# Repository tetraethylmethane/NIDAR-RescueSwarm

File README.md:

<h1 align="center">NIDAR RescueSwarm</h1>

<p align="center">
  Three autonomous drones that search a flood zone, find survivors, geotag them,<br>
  and drop medical kits — with no network, no pilot, and one operator who only presses start.
</p>

<p align="center">
  <b>NIDAR 2026–27 · Track 1 · Mission 1</b><br>
  <sub>MeitY · Drone Federation of India · SwaYaan</sub>
</p>

---

## 1. Status

**Phase 0/1.** Sized end to end, requirements baselined against the rulebook, and the ground station runs as a system against three real ArduCopter SITL autopilots.

**What exists:** coverage planner, geotag geometry and its error model, ArduPilot parameter sets, safety-link protocol, ground station. All tested — 129 + 17 + 67 tests, 13 committed model outputs.

**What does not:** the aircraft, and the detector. There is **no camera anywhere in the loop**; survivors have only ever come from a simulator. Nothing has flown on hardware.

<p align="center">
  
  <br>
  <sub>Three real autopilots flying the coverage planner's output in AUTO, in 6 m/s wind, over locally cached imagery. Every number came from an autopilot.<br>
  ▶ <a href="ground-station/mission-flight.mp4">mission-flight.mp4</a> · <a href="ground-station/README.md">ground-station/README.md</a></sub>
</p>

### Next actions

| # | Action | When | Why first |
|:--|:--|:--|:--|
| 1 | [Send the organiser questions](docs/requirements/organiser-questions.md) — drafted | This week | External latency; nothing else here has any |
| 2 | Start collecting recall data | P1 | The long pole. 250 points, irreducible calendar cost |
| 3 | Bench the cold-boot timing | P1 | The only constraint under 20 % margin, still modelled |

Registration Aug 2026 · reviews Oct and Dec · **finals Jan 2027**. About 21 weeks, but monsoon and exams cut the **flight-test window to ~8 weeks**. See the [development plan](docs/development-plan.md).

---

## 2. Design point

Outputs of a closed model in [`tools/sizing-model/`](tools/sizing-model/), reconciled with the BOM to ~2 %.

| Aircraft | | Mission | |
|:--|:--|:--|:--|
| Configuration | Quadrotor · 18 in CF folding props | Design mission | **7.7 min** of 30 |
| Battery | 6S3P 21700 · 18 cells · 292 Wh | Search | 60 m AGL at 8 m/s |
| MTOW | 6.36 kg *(model)* · 6.23 kg *(BOM)* | Sweep | 93 s/drone, 10 ha over 3 |
| **Fleet** | **19.1 kg** of 25 kg — 24 % margin | GSD | 1.82 cm/px — a person is ~93 px |
| Hover | 913 W · 9.7 kg/m² disk loading | Link | ≥13 dB at 600 m · 2.5 Mbps |
| Endurance | 15.3 min — **≈2.0× the mission** ⚠ | Geotag target | CEP50 ≤ 0.75 m with RTK |
| Thrust-to-weight | 2.0 static · hover at 50 % | Delivery target | ≥60 % within 2 m, ≥30 % within 1 m |

> ⚠ **The reserve is spent.** The 300 g parachute (SYS-41) takes endurance to ≈2.0× against a self-imposed ≥2.0× policy. Any further mass growth breaks it. See [`bom_reconcile.py`](tools/sizing-model/bom_reconcile.py).
>
> **Under review:** 40 m beats 60 m — 140 px on a person instead of 93, for 2.5 min of a 15 min allowance. Pending recall measurement in P7.

---

## 3. Proof

Three ArduCopter SITL instances, the real `rescueswarm-drone{1,2,3}.parm`, the real planned missions. Every number below came off MAVLink. Telemetry is committed in [`simulations/recordings/`](simulations/recordings/); the figures redraw from it.

### 3.1 The battery failsafe brings them home

`BATT_FS_LOW_ACT = 2` had been reviewed and unit-tested for weeks, and **no simulation ever loaded the file** — every SITL script used stock defaults, where the value is `0` and a low battery does nothing at all. Now proven end to end: RTL fires at **10 809 mAh of a 10 800 mAh trip**, on all three aircraft, within two seconds of each other.

### 3.2 They no longer collide

Three defects, none visible in review, all found by running the real artifact:

- **Launches were simultaneous.** Three aircraft leaving slots 1.22 m apart measured 1.3 m from each other at 2–3 m altitude. Now `NAV_DELAY` 0/15/30 s in the mission file.
- **Two of three swept the wrong way round**, finishing 516 m and 540 m from the pad on the lowest state of charge of the flight, because sweep direction keyed on drone index. Now all three finish inside 130 m, same path length.
- **They landed on top of each other.** See §4.

| Separation, three aircraft | Before | After |
|:--|--:|--:|
| Launch, closest pair | 1.31 m | **26.96 m** |
| Whole flight, both airborne | 3.99 m | **5.51 m** |
| Closest horizontal, any time | 0.83 m — *overlap* | **1.89 m** |
| Recovery run, closest at any time | 0.83 m — *overlap* | **2.27 m** |

### 3.3 The search pattern

Each strip is swept twice, the second pass on the reverse heading, and every sweep finishes near the pad.

### 3.4 The pad

> **"Measured" means measured in simulation.** That rules out whole classes of error and none of the physical ones. [HANDOFF.md](HANDOFF.md) §2 keeps measured, modelled and assumed apart.

---

## 4. Decisions

| Decision | Outcome | Why |
|:--|:--|:--|
| Coaxial X8? | **Rejected** | +59–119 % hover power, +34–50 % fleet mass, cuts the margin to 2 %, buys no footprint back, worst attitude bandwidth tested |
| Rotor count | **Quad** | Hex/octo match or beat it on physics, but cost 1.5–2× the propulsion integration on a 21-week calendar. Decided on schedule risk, not physics |
| Prop diameter | **18 in** | Matches the BOM, and better than 20 in on descent (0.42 v_i) and gust sensitivity (0.168) |
| Thrust-to-weight | **2.0** | Tilt only reaches 12° at 15 m/s — attitude authority is never the wind limit |
| Recovery chute | **Fit one** | Cannot meet the "land on the pad" condition, but −10 beats −50, so it is worth ~40 points anyway |
| Pad layout | **Corners, not a row** | A row is the worst packing on a square. Compliance said "3 per row"; they landed **0.83 m** apart — an overlap. Corners give 2.61 m instead of 1.22 m. Measured closest approach **0.83 → 2.27 m** |
| Search pattern | **Two passes, second reversed** | Not for coverage — one pass has no gaps. Boresight bias is *systematic*, so flying the reverse heading cancels it where more frames cannot. Costs a full second sweep |
| Launch and recovery | **Sequenced in the mission file** | `NAV_DELAY` 0/15/30 s and `RTL_LOIT_TIME` 0/60/120 s — parameters, not companion code, because the failsafe RTL is a mode change inside the flight controller. The loiter stagger is 60 s because the descent was **measured** at 53 s; at the 20 s it was first set to, two aircraft closed to 3.10 m over the pad |
| Motor-out redundancy | **Open** | Only rotors keep the aircraft *flying and scoring*, and only rotors work in the 6 m delivery hover. Ties to rotor count |

Numbers in [configuration trade](docs/sizing/configuration-trade.md).

---

## 5. Scoring, and what reading it properly changed

**1000 points:** 600 flight · 200 design review · 200 business strategy.

| Flight — 600 | Points | | Penalty | Cost |
|:--|--:|:--|:--|--:|
| Detection + geotagging | **250** | 25 each, max 10 | Manual input or reset | −50 |
| Kit delivery accuracy | **200** | ≤1 m: 20 · ≤2 m: 14 · ≤3 m: 8 | Crash | −50 |
| Multi-drone collaboration | 50 | binary | Geofence breach | −20 |
| Single GCS interface | 50 | binary | Landing outside the box | −10/drone |
| Finish inside 15 min | 50 | binary | <sub>capped at 150</sub> | |

Three findings that moved the design more than any engineering analysis did:

- **Geolocation gates 450 of 600 points**, not 250. Kits are scored from the survivor, so a drop is never better than the tag it aimed at. RTK alone is worth 82 delivery points.
- **We were designing to the worst zone.** The old ≤3 m target scored 8 of 20 per drop; the old "90 % within 5 m" requirement sat outside every zone and would have scored nothing.
- **Speed is worth 50 points and is already won.** The bonus needs 15 min; we fly 7.7. Spend the surplus on recall — fly lower, take more looks.

Full breakdown in [rulebook compliance](docs/requirements/rulebook-compliance.md).

---

## 6. Open

| Risk | Detail | Status |
|:--|:--|:--|
| **Setup margin** | 15 s against a 5-minute rule — modelled, not measured | Recovered by SYS-42/43; bench in P1 |
| **VRS on every delivery** | 2.5 m/s descent sits at 0.48 v_i, on the vortex-ring boundary | Fix in the flight profile, not the airframe |
| **Wind cliff at 8 m/s** | Search groundspeed is 8 m/s, so at that windspeed we make no headway. Wind is natural and uncapped | Requirement: 10 m/s headway (SYS-37) |
| **Business strategy** | 200 points, barely started; sponsorship evidence cannot be produced in the final week | Start now |

Four questions are [drafted and unsent](docs/requirements/organiser-questions.md) — how "correctly geotagged" is verified, whether a canopy descent scores −10 or −50, whether motor-out tolerance is required, and whether the pad can be surveyed beforehand. The first decides whether ~1–2 m of absolute base error costs anything against 250 points. Answers already received are recorded in the same file.

---

## 7. Repository

```text
HANDOFF.md                  read this first if you are picking the project up
TRAPS.md                    read this before adding a config, a generated file or a test
docs/                       requirements, sizing, business, system overview
tools/sizing-model/         the model everything traces back to
hardware/bom/               Indian BOM + indigenisation scorecard
autonomy/coverage_planner/  boundary in, one AUTO mission per drone out
perception/geotagging/      pixel to lat/lon, and a Monte Carlo of its error
firmware/ardupilot-params/  the five failsafes, as parameters not code
simulations/                SITL harness, committed telemetry, figures
ground-station/             mission_backend + the GCS engineering record
```

The **running** ground station — Flask server, React client, SITL launch scripts — is in [NIDAR-GSC](https://github.com/tetraethylmethane/NIDAR-GSC). What lives here is `ground-station/mission_backend/` (fleet model, KML parser, MAVLink ingest, and the SYS-20 module split that makes a retask route structurally unreachable), plus the requirement evidence: [PLAN.md](ground-station/PLAN.md), the flight screenshots and [mission-flight.mp4](ground-station/mission-flight.mp4).

> ⚠ **The two copies of `mission_backend` have drifted.** `mavlink_ingest.py` is 186 lines here against 304 in NIDAR-GSC, and only the GSC copy calls `SET_MESSAGE_INTERVAL` — without which a passive listener receives nothing but heartbeats. The GSC copy is the one that flies; this one is what CI tests. See [HANDOFF.md](HANDOFF.md) §4.5.

`communication/` is still planned.

```bash
pip install -r tools/sizing-model/requirements.txt
python3 tools/sizing-model/rescueswarm_sizing_model.py   # the design point
python3 tools/sizing-model/bom_reconcile.py              # read before ordering

export NIDAR_SYS=$PWD
../NIDAR-GSC/scripts/test-battery-failsafe.sh            # low battery brings it home
python3 simulations/sitl/fly_and_record.py               # three aircraft fly the plan
python3 simulations/sitl/proof_figures.py                # redraw §3 from telemetry
```

`NIDAR_SPEEDUP=3` slows the sim enough to see the launch stagger. Do **not** use `NIDAR-GSC/scripts/run-sim.sh` — it launches a fixed wing with no project parameters.

> **Change the model, re-run it, commit the new output in the same commit.** Every number in this README traces to [`docs/sizing/`](docs/sizing/), and CI fails if one drifts.

| Document | What's in it |
|:--|:--|
| [Handoff](HANDOFF.md) | **Start here.** What is proven, what waits on a human, what is unowned |
| [Traps](TRAPS.md) | Ten classes of defect this project has already paid for, and what now prevents each |
| [Competition day](docs/checklists/competition-day.md) | How the GCS is actually operated on the day — draft, never rehearsed |
| [System overview](docs/system-overview.md) | Mission flow, architecture, perception, indigenisation, failsafes |
| [Sizing calculations](docs/sizing/sizing-calculations.md) | Why every number is what it is |
| [Requirements baseline](docs/requirements/requirements-baseline.md) | Every SYS-xx requirement, traced to a rule and a verification method |
| [Rulebook compliance](docs/requirements/rulebook-compliance.md) | Rule-by-rule matrix, scoring, conflicts |
| [Development plan](docs/development-plan.md) | Schedule, critical path, risk and de-scope order |
| [Implementation plan](docs/implementation-plan.md) | What to build for autonomy, perception and failsafes — and what can be skipped |
| [Frame design constraints](docs/frame-design-constraints.md) | What CAD needs before the first part is cut |

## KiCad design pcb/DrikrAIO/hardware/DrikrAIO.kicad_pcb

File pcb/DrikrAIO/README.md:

# DrikrAIO — Stage 1

Single-board integration of a flight controller, four ESC channels and an
ExpressLRS receiver, assembled from proven OpenDrone designs.

**Status: schematic netlists; board is a placed scaffold, unrouted.** See *Open work*.

This is Stage 1 of two. It deliberately targets FPV-class hardware on the parts
that already fly, to prove the integration once. Stage 2 re-platforms to
ArduPilot on a Pixhawk Autopilot Bus carrier and reuses the power tree, ESC
block and layout zoning proven here.

## Licence and attribution

**CERN-OHL-S-2.0, strongly reciprocal**, inherited from the upstream sources.
Every sheet in `hardware/` is copied from an [OpenDrone-hw](https://github.com/OpenDrone-hw)
project by @Just4Stan / incutec. This board is a derivative work; its complete
sources are published under the same licence, as that licence requires.

| Sheet | Copied from | Upstream status |
|---|---|---|
| `rp2350a`, `power`, `imu`, `osd`, `blackbox`, `pads` | OpenFC-Lite-Mini rev3.3 | Shipping. Rev2 flown. |
| `ESC` (×4) | OpenESC-30x30 rev3.3 | Shipping. Rev1 validated build. |
| `rx_esp32c3_sx1281` | OpenAIO (itself from OpenRX-Lite) | Routed, never manufactured |
| `esc_power` | OpenESC-30x30 rev3.3 root sheet | Shipping |
| `KiCad-Library/` | OpenDrone-hw/KiCad-Library | Shared parts catalogue |

## Design decisions

**40 V MOSFETs, not 30 V.** OpenAIO uses the DOY180N03T, 30 V, which on a 6S
pack at 25.2 V leaves 1.19× margin — below what half-bridge ringing reaches.
The `ESC` sheet is taken from OpenESC-30x30 instead, which uses the 40 V
SP40N01GHNK at 1.59× and is rated to 8S. This is why the ESC sheet comes from
the 30×30 rather than from OpenAIO.

**30.5 × 30.5 mm mount.** Four PDFN-8L 5×6 power stages do not fit on OpenAIO's
25.5 mm — that is precisely why upstream used the smaller 30 V part. The larger
mount also removes the crowding that left OpenAIO with 74 unrouted pads.

**Two power trees, kept separate.** The FC sheet makes +10 V, +5 V, +3V3 and
+1V8; the ESC needs its own +10 V gate rail and +3V3. They are **not** merged.
The FC's +10 V is gated by `10V_ENABLE` (a firmware PINIO, there to switch a
VTX), and a firmware toggle that cuts gate drive in flight is not a rail an ESC
may share. The ESC keeps the LMR54406 buck and TLV76733 LDO from OpenESC-30x30.

**SX1281, 2.4 GHz.** Not the dual-band LR1121. The 865–867 MHz safety link
([`communication/safety_link/`](../../communication/safety_link/)) must be a
physically separate radio: the reason to abort is usually that the primary link
has failed, so an abort path sharing that radio is not an abort path.

## Reference bands

Each sheet numbers into its own band, so a reference says which block it is in
and nothing collides. The four ESC channels share one file and are distinguished
by band.

| Band | Sheet | | Band | Sheet |
|---|---|---|---|---|
| 1xx | rp2350a | | 6xx | pads |
| 2xx | power | | 7xx | rx |
| 3xx | imu | | 11xx | ESC channel 1 |
| 4xx | osd | | 12xx | ESC channel 2 |
| 5xx | blackbox | | 13xx | ESC channel 3 |
| 8xx | esc_power | | 14xx | ESC channel 4 |

## State

```
components 347      nets 332      sheets 12
ERC        30 errors, 546 warnings
```

**The 30 errors are inherited, not introduced.** The donor boards report the
same classes: OpenFC-Lite-Mini, which has flown, reports 8 `power_pin_not_driven`,
and OpenESC-30x30, in production, reports 24 `pin_not_driven` and 3
`power_pin_not_driven`. Summed across what we instantiate, the donor baseline is
about 37; this design sits below it. `PWR_FLAG`s were tried on +BATT and GND and
removed again -- they cleared none of the old errors and added two new
`label_dangling`, and a new error type is a regression where an existing one is
not. Resolve these in KiCad against the real symbols.

Most of the warnings are the same story: `pin_to_pin` inherited from the donor
sheets, plus unresolved `ESCLibrary` / `PCM_*` symbol libraries, which are KiCad
PCM add-ons. Symbols are embedded in the schematics, so the design opens and
netlists without them; install them only to re-place those parts.

## Board

`DrikrAIO.kicad_pcb` exists as a **scaffold, not a layout**. 50 x 50 mm on the
30.5 mm mounting pattern, 6 layers, 2 oz outer / 1 oz inner, ENIG. Nothing is
routed.

```
50 x 50 mm      6 layers      347 footprints      1283 pads netted
292 placed on board            55 staged off-board, grouped by block
0 overlaps                     0 parts crossing the edge
```

Placement is by function: power stages in four quadrants on the bottom with
the shared power block across the middle, control on top, receiver in a corner
for the antenna. Where a zone filled up the remainder is staged **outside** the
outline in per-block columns, which is what KiCad does with new parts -- better
an honestly unplaced part than one silently overlapping its neighbour.

**Board size was measured, not chosen.** U3's pad set alone spans 44.0 x 45.8 mm
so 45 mm could not contain it, and the other 346 parts come to 2409 mm2 of
footprint area -- 48 % of a two-sided 50 mm board, which leaves room to route.

Rebuild it with:

```sh
"C:/Program Files/KiCad/10.0/bin/python.exe" hardware/tools/build_pcb.py
```

## Reviews

# ROUTING STATUS: BLOCKED — BASELINE FROZEN

**[docs/routing-readiness-report.md](docs/routing-readiness-report.md) is current.**
Baseline rev 3, frozen: [docs/pre-routing-baseline.json](docs/pre-routing-baseline.json),
[docs/freeze-manifest.json](docs/freeze-manifest.json).

Verify the freeze at any time:

```sh
python hardware/tools/freeze.py     # exit 0 = intact
```

Primary remaining thermal variables are **airflow exposure and duty cycle**.
More copper is **not** the primary solution.

Blocked on: 115 A peak duration, peak repetition rate, airflow boundary
condition, thermal validation plan, and the deferred MOSFET schematic commit.

**Thermal is MARGINAL, not PASS.** Only one steady-state case passes — hover in
developed slipstream (103.2 C). Peak fails the 125 C target at both airflows
(132.7 C slipstream, 169.9 C at the disc). Still air reaches 393 C and is
prohibited above quiescent.

The result that redirects the work: Rth(j-c) + R_spread contribute only **5.7 K**
of the rise. **More vias and more copper cannot fix the peak case** — the
bottleneck is board-to-air. The only levers are airflow exposure and duty cycle.

The result that may make it moot: board time constant is **31-45 s**, so a peak
much shorter than that barely moves the board. At h=60, duty up to 0.5 stays
under target. But duty cycle is OPEN, so no row can be selected.

Analysis: [docs/thermal-analysis.md](docs/thermal-analysis.md) ·
Validation: [docs/thermal-validation-plan.md](docs/thermal-validation-plan.md)

## Electrical design review

**[docs/electrical-design-review.md](docs/electrical-design-review.md) gates
routing.** Numbers regenerate from `hardware/tools/power_review.py`.

**Resolved:** `Phase` and `VBAT` netclasses corrected 1.0 mm → 6.6 mm with
0.8/0.4 vias (1.0 mm carries 5.3 A against a 21 A phase RMS), and the MOSFET
decision is **60 V minimum**.

**Preferred part: Infineon BSC014N06NS**, verified against the manufacturer
datasheet (Rev 2.6) in [docs/pre-routing-report.md](docs/pre-routing-report.md).
Package is **PG-TDSON-8**. Land pattern **passes** the arithmetic against
`PDFN-8L_L6.0-W5.0-P1.27`; the **stencil does not** — the thermal pad has one
18 mm² paste aperture where Infineon specifies a windowpane, a defect the
current OpenESC footprint already carries. Loop budget corrected to **8.72 nH**
on the real t_f of 11 ns, 3.9× the 40 V part. Not committed to the schematic.

**The headline current is not board capability:** 257 A is at T_c=25 °C. On a
PCB in still air the datasheet says **31 A**, assuming 6 cm² of copper per
device — and 24 FETs on a 50 × 50 board get about 2.1 cm² each.

**Still open: the 115 A peak duration** is undefined anywhere in the repo, so
repeated peaks cannot be assessed. Firmware parameter, not a PCB one.

Also established: 115 A needs 69 mm of 2 oz outer copper on a 50 mm board, so
the bus must use **all six layers**; J1 is 0.7 A per contact and is a breakout
only, never a battery path; and the board is cooled by propwash — at peak in
still air it reaches ~110 °C.

## Open work

1. **Routing, and real placement.** The scaffold groups parts correctly; it does
   not lay them out. Four switching power stages, a 2.4 GHz chain and a 115 A
   battery entry share this board, and that is judgement work, not a generator's.
   Start by pulling the 55 staged parts in and putting the IMU near the board
   centre -- the scaffold parks it at the right edge for want of a free zone.
2. **Review the generated root in KiCad.** `DrikrAIO.kicad_sch` was produced by
   a script, not drawn. It wires sheets with global labels on stubs, which is
   electrically correct and reviewable, but it is not a drawn schematic.
3. **Resolve the 30 inherited ERC errors** against the real symbols, or record
   them as accepted the way the donor projects do.
4. **`+3.3V` and `+3V3` are different nets** -- the FC rail and the ESC rail,
   deliberately separate per the power-tree decision above. The names differ by
   one character and mean different things, which is a trap. Consider renaming
   the FC rail to `+3V3_FC` before layout.

### Done

Board power entry, ESC current sense and the motor pads all arrived with
`esc_power`. `U3` in that sheet is not a board outline -- an earlier pass
mistook it for one and deleted it -- it is the ESC's whole pad set: VBAT,
BATGND, CUR, M1-M4 and the twelve phase pads 1A..4C. Verified in the netlist:
`ESC_CURRENT` reaches the FC ADC, `+10V` reaches all four gate-driver rails,
`M1_A` runs from the channel-1 MOSFETs to its pad, and `MOTOR1` runs from the
FC MCU to the channel-1 DShot input.

## Build

Every sheet here is a rewritten copy of a donor. That rewrite is not
idempotent, so rebuild the whole set rather than editing in place:

```sh
bash hardware/tools/regen.sh
```

```sh
kicad-cli sch erc hardware/DrikrAIO.kicad_sch
kicad-cli sch export netlist --format kicadsexpr -o /tmp/DrikrAIO.net hardware/DrikrAIO.kicad_sch
```

Requires KiCad 10. The files are KiCad 10 format and KiCad 8 cannot open them.

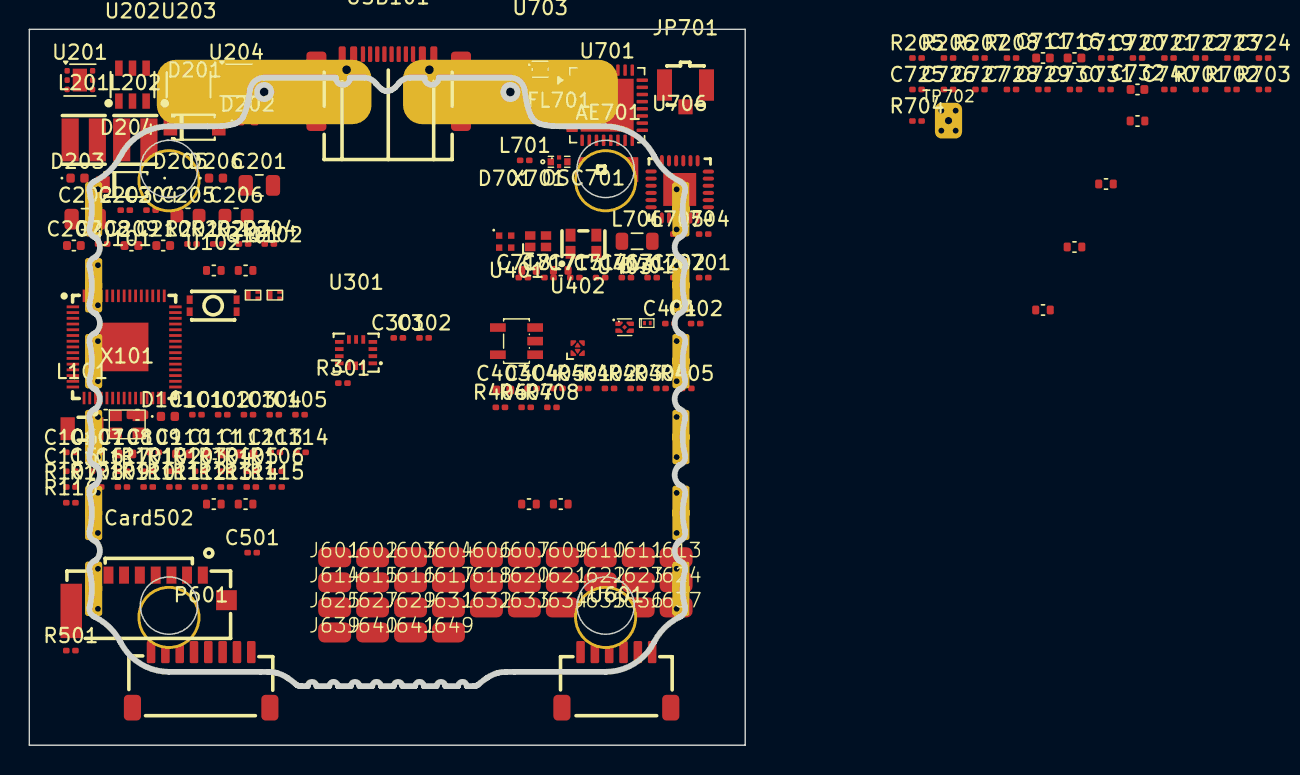
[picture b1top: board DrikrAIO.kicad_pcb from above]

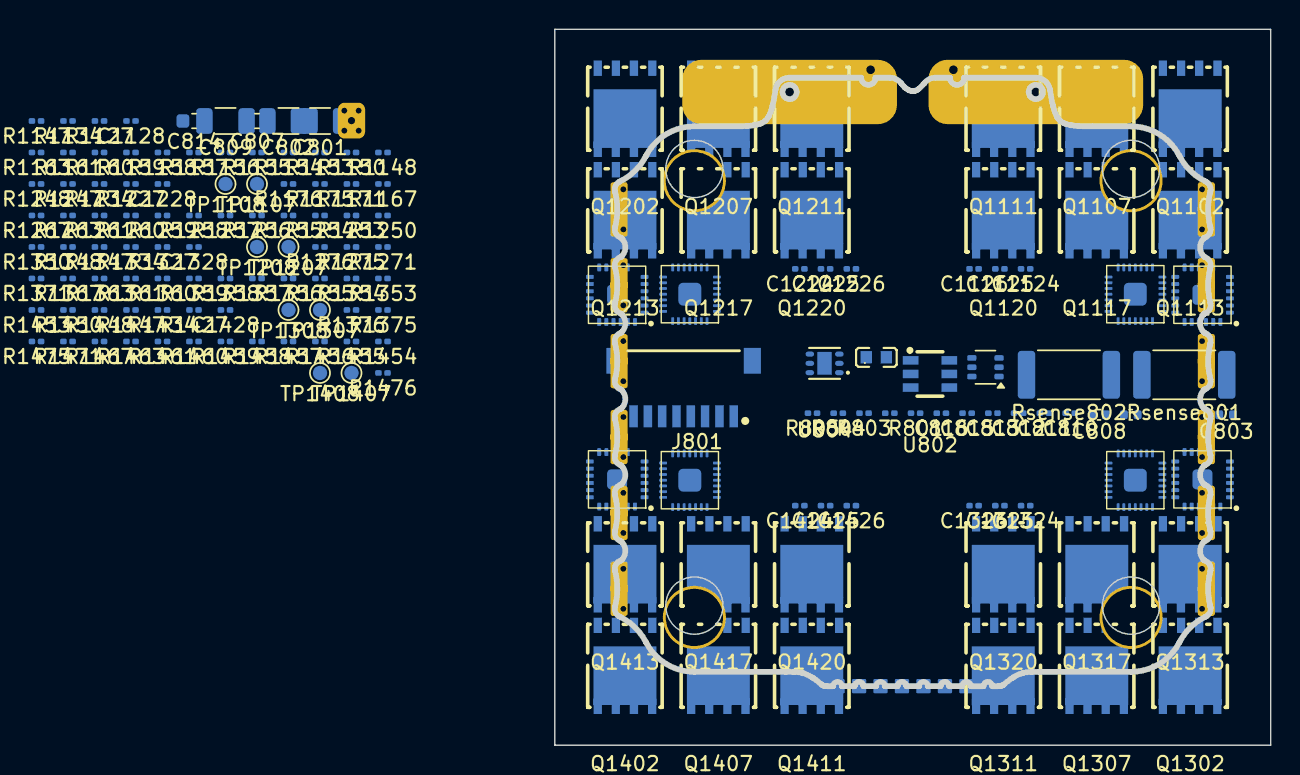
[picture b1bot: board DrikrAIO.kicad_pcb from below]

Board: 6 copper layers, 50.0 x 50.0 mm, 347 parts (173 on the bottom side), 243 nets, no tracks yet.

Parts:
AE701: 2450AT18A100E; ANT-SMD_L3.2-W1.6
C101, C103, C104, C105, C106, C107, C109, C113, C115, C116, C117, C203, C204, C208, C301, C302, C402, C404, C405, C501: 100n; C_0201_0603Metric
C102, C114: 20p; C_0201_0603Metric
C108, C110, C111, C112, C207: 4.7uF; C_0402_1005Metric
C201, C202: 4.7uF 50v; C_0805_2012Metric
C205, C206, C807, C814: 22uF; C_0603_1608Metric
C209, C210, C803, C808: 22uF; C_0402_1005Metric
C401: 470p; C_0201_0603Metric
C403, C806: 1uF; C_0402_1005Metric
C701, C728: 15pF; C_0201_0603Metric
C702, C715, C722, C724, C727, C729: 1uF; C_0201_0603Metric
C711, C716, C732: 10uF; C_0402_1005Metric
C712, C713, C714, C717, C730, C731, C740, C810, C811, C812, C813, C815, C816, C1124, C1125, C1126, C1128, C1224, C1225, C1226, C1228, C1324, C1325, C1326, C1328, C1424, C1425, C1426, C1428: 100nF; C_0201_0603Metric
C718: 1nF; C_0201_0603Metric
C719: 470nF; C_0201_0603Metric
C720, C721: 1.2pF; C_0201_0603Metric
C723, C725, C726: 10nF; C_0201_0603Metric
C801, C802, C809: 4.7uF; C_1206_3216Metric
C804, C805, C1104, C1108, C1127, C1204, C1208, C1227, C1304, C1308, C1327, C1404, C1408, C1427: 100nF; C_0402_WIDE
Card502: TF-021B-H265; TF-SMD_TF-021B-H265
D101: LED_1_Blue; LED_0402_1005Metric
D201, D204: DSK24; SOD-123_L2.8-W1.8-LS3.7-RD
D202, D203, D205, D206: LED_1_Green; LED_0402_1005Metric
D401: SDM02U30LP3-7B; X3-DFN0603-2_L0.6-W0.3-RD
D701: XL-1010RGBC-WS2812B; LED-SMD_4P-L1.0-W1.0-TL_XL-1010RGBC-WS2812B
FL701: 2450FM07D0034T; FILTER-SMD_4P-L1.0-W0.5-L
J601, J602, J603, J604, J606, J607, J609, J610, J611, J613, J614, J615, J616, J617, J618, J620, J621, J622, J623, J624, J625, J627, J629, J631, J632, J633, J634, J635, J636, J637, J639, J640, J641, J649: 5V; small_pad
J801: SM08B-SRSS-TB; JST_SM08B-SRSS-TB
JP701: U.FL-R-SMT-1(80); RF-SMD_FRF05002-JSS103M
L101: AOTA-B201610S3R3-101-T; IND-SMD_L2.0-W1.6_AOTA-B201610S3R3-101-T
L201, L202: XRTC303020D4R7MBCA; IND-SMD_L3.0-W3.0_AFE303020S
L701: 24nH; L_0201_0603Metric
L704: 2.5nH; L_0201_0603Metric
L705: 2.0nH; L_0201_0603Metric
L706: 15uH; L_0805_2012Metric
OSC701: OW7EL89CENUNFAYLC-52M; OSC-SMD_4P-L2.0-W1.6-BL_TXC_7Z
P601: SM08B-SRSS-TB(LF)(SN); CONN-TH_SM08B-SRSS-TB-LF-SN
Q101, Q102: AP1606; DFN-3L_L1.0-W0.6-P0.65-BR
Q1102, Q1107, Q1111, Q1113, Q1117, Q1120, Q1202, Q1207, Q1211, Q1213, Q1217, Q1220, Q1302, Q1307, Q1311, Q1313, Q1317, Q1320, Q1402, Q1407, Q1411, Q1413, Q1417, Q1420: SP40N01GHNK; PDFN-8L_L6.0-W5.0-P1.27
R101, R104, R201, R203: 100k; R_0201_0603Metric
R102, R105, R107: 30R; R_0201_0603Metric
R103, R108, R301, R501, R701, R702, R703, R704, R802, R1147, R1148, R1247, R1248, R1347, R1348, R1447, R1448: 10k; R_0201_0603Metric
R106, R109, R114, R115: 5.1k; R_0201_0603Metric
R110, R116: 1k; R_0201_0603Metric
R111, R208: 2.4k; R_0201_0603Metric
R112, R113, R401, R408: 75R; R_0201_0603Metric
R202, R206: 6.49k; R_0201_0603Metric
R204: 13.7k; R_0201_0603Metric
R205: 7.5k; R_0201_0603Metric
R207, R406, R407: 510R; R_0201_0603Metric
R402: 3.9k; R_0201_0603Metric
R403: 12k; R_0201_0603Metric
R404: 1.4k; R_0201_0603Metric
R405: 680R; R_0201_0603Metric
R801: 115k; R_0201_0603Metric
R803, R804, R805, R1154, R1157, R1160, R1254, R1257, R1260, R1354, R1357, R1360, R1454, R1457, R1460: 1k; C_0201_0603Metric
R1127, R1134, R1150, R1163, R1167, R1171, R1227, R1234, R1250, R1263, R1267, R1271, R1327, R1334, R1350, R1363, R1367, R1371, R1427, R1434, R1450, R1463, R1467, R1471: 15R; R_0201_0603Metric
R1153, R1155, R1156, R1158, R1159, R1161, R1253, R1255, R1256, R1258, R1259, R1261, R1353, R1355, R1356, R1358, R1359, R1361, R1453, R1455, R1456, R1458, R1459, R1461: 10k; C_0201_0603Metric
R1175, R1275, R1375, R1475: 220R; R_0201_0603Metric
R1176, R1276, R1376, R1476: 10R; R_0201_0603Metric
Rsense801, Rsense802: 0.2mR; R_2512_6332Metric
TP702: BOOT; SolderPad_1.2x2.0mm
TP1107, TP1108, TP1207, TP1208, TP1307, TP1308, TP1407, TP1408: TestPoint; TestPoint_Pad_D1.0mm
U101: RP2354A; QFN-60_L7.0-W7.0-P0.40-TL-EP3.4
U102: TS2306A 240GF MSM 9_C2976675; SW-SMD_4P-L3.0-W2.0-P0.85-LS3.5
U201: LP5912-1.8DRVR; WSON-6-1EP_2x2mm_P0.65mm_EP1x1.6mm_ThermalVias
U202, U203: LMR51430YFDDCR; SOT-23-6_L2.9-W1.6-P0.95-LS2.9-BL
U204: LP5912-3.3DRVR; WSON-6-1EP_2x2mm_P0.65mm_EP1x1.6mm
U301: BMI270; LGA-14_L3.0-W2.5-P0.50-BR
U401: COS8051SOT; SOT-23-5_L3.0-W1.7-P0.95-LS2.8-BR
U402: SN74LVC1G3157DTBR; X2SON-6_L1.0-W0.8-BL
U403: TLV7031DPWR; X2SON-4_L0.8-W0.8-P0.48-TL-A
U601: SM06B-SRSS-TB(LF)(SN); CONN-SMD_SM06B-SRSS-TB-LF-SN
U701: ESP32-C3; QFN-32-1EP_5x5mm_P0.5mm_EP3.7x3.7mm
U703: TLV75533PDQNR; X2SON-4_L1.0-W1.0-P0.65-TL-EP
U706: SX1281IMLTRT; QFN-24_L4.0-W4.0-P0.50-TL-EP2.6
U801: INA186A3IDCKR; SOT-363_SC-70-6
U802: LMR54406DBVR; SOT-23-6_L2.9-W1.6-P0.95-LS2.8-BR
U803: FTC160808S4R7MBCA; IND-SMD_L1.6-W0.8_FTC160865SR47MBCA
U804: TLV76733DRVR; WSON-6_L2.0-W2.0-P0.65-TL-EP
U805: 4in1ESC30x30
U1101, U1201, U1301, U1401: NSG2065Q; QFN-24_L4.0-W4.0-P0.50-TL-EP2.8
U1108, U1208, U1308, U1408: AT32F421G8U7; QFN-28_L4.0-W4.0-P0.40-TL-EP2.4
USB101: TYPE-C 16P QTWT; USB-TYPE-C-SMD_TYPE-C-16P-QTWT
X101: XTM25012000JT00351001; CRYSTAL-SMD_4P-L2.5-W2.0-BL-A
X701: CJ17-400001010B20; CRYSTAL-SMD_4P-L1.6-W1.2-BL

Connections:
10V_ENABLE: U101.41, U202.5
+1.1V: C101.1, C107.1, C108.1, C112.1, L101.1, U101.6, U101.23, U101.39, U101.50
+1.8V_GYRO: C209.1, C301.1, U201.1, U301.8
+3.3V: C103.1, C104.1, C105.1, C111.1, C113.1, C115.1, C116.1, C117.1, C210.1, C302.1, C402.1, C404.1, C405.1, C501.1, Card502.4, J617.1, R102.1, R114.1, R115.1, R207.1, R301.2, R403.2, R501.1, U101.1, U101.11, U101.20, U101.26, U101.30, U101.38, U101.44, U101.45, U101.49, U101.53, U101.54, U204.1, U301.5, U401.5, U402.5, U403.2
+3V3: C711.1, C712.1, C713.1, C714.1, C715.1, C716.1, C717.1, C722.1, C723.1, C729.1, C730.1, C731.1, C740.1, C803.2, C808.2, C813.1, C815.1, C1126.1, C1226.1, C1326.1, C1426.1, D701.2, L705.2, OSC701.4, R701.1, R702.1, R703.1, R704.2, R1147.2, R1176.2, R1247.2, R1276.2, R1347.2, R1376.2, R1447.2, R1476.2, U701.11, U701.17, U701.18, U701.31, U701.32, U703.1, U706.11, U706.15, U801.3, U804.1, U804.2, U1108.17, U1208.17, U1308.17, U1408.17
+4v5: C207.1, C208.1, C702.1, C732.1, D201.1, D204.1, J631.1, J641.1, R206.1, U201.4, U201.6, U204.4, U204.6, U703.3, U703.4
+5V: C206.1, D204.2, J606.1, J611.1, J614.1, J620.1, L202.2, R111.1, R203.2, R208.1
+5V_USB: D201.2, USB101.A4, USB101.A9
+10V: C205.1, C807.1, C812.1, C814.1, C1128.1, C1228.1, C1328.1, C1428.1, J636.1, L201.2, R201.2, R205.1, R801.1, U601.1, U803.2, U804.4, U804.6, U1101.4, U1201.4, U1301.4, U1401.4
+BATT: C201.1, C202.1, C801.1, C802.1, C809.1, C810.1, J618.1, J801.1, P601.1, Q1102.3, Q1111.3, Q1113.3, Q1202.3, Q1211.3, Q1213.3, Q1302.3, Q1311.3, Q1313.3, Q1402.3, Q1411.3, Q1413.3, R101.2, R804.2, Rsense801.2, Rsense802.2, U202.3, U203.3, U203.5, U802.4, U802.5, U805.3
/esc1/AH: U1101.22, U1108.20
/esc1/AL: U1101.1, U1108.15
/esc1/BH: U1101.23, U1108.19
/esc1/BL: U1101.2, U1108.14
/esc1/CH: U1101.24, U1108.18
/esc1/CL: U1101.3, U1108.13
/esc1/FBA: R1153.1, R1154.2, R1155.2, U1108.6
/esc1/FBB: R1156.2, R1157.2, R1158.2, U1108.10
/esc1/FBC: R1159.2, R1160.2, R1161.2, U1108.11
/esc1/FBCOMMON: R1153.2, R1156.1, R1159.1, U1108.7
/esc1/GHA: R1167.1, U1101.19
/esc1/GHB: R1150.1, U1101.16
/esc1/GHC: R1127.1, U1101.13
/esc1/GLA: R1171.1, U1101.11
/esc1/GLB: R1163.1, U1101.10
/esc1/GLC: R1134.1, U1101.9
/esc1/vdda: C1125.1, R1176.1, U1108.5
/esc2/AH: U1201.22, U1208.20
/esc2/AL: U1201.1, U1208.15
/esc2/BH: U1201.23, U1208.19
/esc2/BL: U1201.2, U1208.14
/esc2/CH: U1201.24, U1208.18
/esc2/CL: U1201.3, U1208.13
/esc2/FBA: R1253.1, R1254.2, R1255.2, U1208.6
/esc2/FBB: R1256.2, R1257.2, R1258.2, U1208.10
/esc2/FBC: R1259.2, R1260.2, R1261.2, U1208.11
/esc2/FBCOMMON: R1253.2, R1256.1, R1259.1, U1208.7
/esc2/GHA: R1267.1, U1201.19
/esc2/GHB: R1250.1, U1201.16
/esc2/GHC: R1227.1, U1201.13
/esc2/GLA: R1271.1, U1201.11
/esc2/GLB: R1263.1, U1201.10
/esc2/GLC: R1234.1, U1201.9
/esc2/vdda: C1225.1, R1276.1, U1208.5
/esc3/AH: U1301.22, U1308.20
/esc3/AL: U1301.1, U1308.15
/esc3/BH: U1301.23, U1308.19
/esc3/BL: U1301.2, U1308.14
/esc3/CH: U1301.24, U1308.18
/esc3/CL: U1301.3, U1308.13
/esc3/FBA: R1353.1, R1354.2, R1355.2, U1308.6
/esc3/FBB: R1356.2, R1357.2, R1358.2, U1308.10
/esc3/FBC: R1359.2, R1360.2, R1361.2, U1308.11
/esc3/FBCOMMON: R1353.2, R1356.1, R1359.1, U1308.7
/esc3/GHA: R1367.1, U1301.19
/esc3/GHB: R1350.1, U1301.16
/esc3/GHC: R1327.1, U1301.13
/esc3/GLA: R1371.1, U1301.11
/esc3/GLB: R1363.1, U1301.10
/esc3/GLC: R1334.1, U1301.9
/esc3/vdda: C1325.1, R1376.1, U1308.5
/esc4/AH: U1401.22, U1408.20
/esc4/AL: U1401.1, U1408.15
/esc4/BH: U1401.23, U1408.19
/esc4/BL: U1401.2, U1408.14
/esc4/CH: U1401.24, U1408.18
/esc4/CL: U1401.3, U1408.13
/esc4/FBA: R1453.1, R1454.2, R1455.2, U1408.6
/esc4/FBB: R1456.2, R1457.2, R1458.2, U1408.10
/esc4/FBC: R1459.2, R1460.2, R1461.2, U1408.11
/esc4/FBCOMMON: R1453.2, R1456.1, R1459.1, U1408.7
/esc4/GHA: R1467.1, U1401.19
/esc4/GHB: R1450.1, U1401.16
/esc4/GHC: R1427.1, U1401.13
/esc4/GLA: R1471.1, U1401.11
/esc4/GLB: R1463.1, U1401.10
/esc4/GLC: R1434.1, U1401.9
/esc4/vdda: C1425.1, R1476.1, U1408.5
/esc_power/CSA+: R805.2, Rsense801.1, Rsense802.1, U805.1
/osd/OSD_LVL: R402.2, R403.1, R404.2, U402.1
/osd/VID_DC: C403.2, D401.1, U403.4
/osd/VID_FILT: C401.1, C403.1, R405.1
/power/1.8V_PG: D206.2, R206.2, U201.3
/rp2350a/ADC_VBAT: C109.2, R101.1, R103.2, U101.43
/rp2350a/BEEPER: Q101.1, R104.2, U101.28
/rp2350a/D+: R107.2, USB101.A6, USB101.B6
/rp2350a/D-: R105.1, USB101.A7, USB101.B7
/rp2350a/ESC_CURR: C106.1, R116.2, U101.42
/rp2350a/LED0: R112.1, U101.40
/rp2350a/LED_STRIP_L: Q102.1, U101.12
/rp2350a/XIN: C114.2, U101.21, X101.1
/rp2350a/XOUT: R110.1, U101.22
/rx/BOOT: R703.2, TP702.1, U701.15
/rx/BUSY: U701.8, U706.7
/rx/CHIP_EN: C727.1, R704.1, U701.7
/rx/DIO1: U701.5, U706.8
/rx/LED: D701.4, R702.2, U701.14
/rx/MISO: U701.10, U706.16
/rx/MOSI: U701.9, U706.17
/rx/NSS: U701.13, U706.19
/rx/RST: R701.2, U701.6, U706.3
/rx/SCK: U701.12, U706.18
/rx/WIFI: AE701.1, C720.1, L704.1
/rx/XTAL_N: C728.1, U701.29, X701.3
/rx/XTAL_P: L701.2, U701.30
BUZZER-: J610.1, Q101.3
ESC_CURRENT: C816.1, J801.3, R116.1, R803.1, U805.5
FLASH_CS: Card502.2, R501.2, U101.33
GND: C101.2, C102.1, C103.2, C104.2, C105.2, C106.2, C107.2, C108.2, C109.1, C110.2, C111.2, C112.2, C113.2, C114.1, C115.2, C116.2, C117.2, C201.2, C202.2, C205.2, C206.2, C207.2, C208.2, C209.2, C210.2, C301.2, C302.2, C401.2, C402.2, C404.2, C405.2, C501.2, C701.2, C702.2, C711.2, C712.2, C713.2, C714.2, C715.2, C716.2, C717.2, C719.1, C720.2, C721.2, C722.2, C723.2, C724.2, C725.1, C726.2, C727.2, C728.2, C729.2, C730.2, C731.2, C732.2, C740.2, C801.2, C802.2, C803.1, C804.2, C805.2, C807.2, C808.1, C809.2, C810.2, C812.2, C813.2, C814.2, C815.2, C816.2, C1124.2, C1125.2, C1126.2, C1128.2, C1224.2, C1225.2, C1226.2, C1228.2, C1324.2, C1325.2, C1326.2, C1328.2, C1424.2, C1425.2, C1426.2, C1428.2, Card502.6, Card502.9, Card502.10, D101.1, D202.1, D203.1, D205.1, D206.1, D401.2, D701.3, FL701.2, FL701.4, J603.1, J609.1, J615.1, J616.1, J621.1, J633.1, J637.1, J801.2, J801.P1, J801.P2, JP701.2, JP701.3, OSC701.1, OSC701.2, P601.2, P601.9, P601.10, Q101.2, Q102.2, Q1107.1, Q1117.1, Q1120.1, Q1207.1, Q1217.1, Q1220.1, Q1307.1, Q1317.1, Q1320.1, Q1407.1, Q1417.1, Q1420.1, R103.1, R104.1, R106.1, R109.1, R202.2, R204.2, R401.2, R404.1, R406.2, R802.2, R1148.2, R1154.1, R1157.1, R1160.1, R1248.2, R1254.1, R1257.1, R1260.1, R1348.2, R1354.1, R1357.1, R1360.1, R1448.2, R1454.1, R1457.1, R1460.1, U101.47, U101.61, U102.1, U201.5, U201.7, U202.1, U203.1, U204.3, U204.5, U204.7, U301.2, U301.3, U301.6, U301.7, U401.2, U402.2, U403.3, U403.5, U601.2, U601.5, U601.7, U601.8, U701.16, U701.33, U703.2, U703.5, U706.13, U706.20, U706.21, U706.23, U706.24, U706.25, U801.1, U801.2, U802.2, U804.3, U804.5, U804.7, U805.2, U805.4, U805.11, U1101.6, U1101.25, U1108.16, U1108.29, U1201.6, U1201.25, U1208.16, U1208.29, U1301.6, U1301.25, U1308.16, U1308.29, U1401.6, U1401.25, U1408.16, U1408.29, USB101.0, USB101.A1, USB101.A12, X101.2, X101.4, X701.2, X701.4
GYRO_CS: R301.1, U101.17, U301.12
GYRO_INT: U101.13, U301.4
I2C0.SCL: J604.1, R114.2, U101.8
I2C0.SDA: J607.1, R115.2, U101.7
LED_STRIP: J601.1, J613.1, Q102.3, R111.2
M1_A: C1127.1, Q1111.1, Q1120.3, R1155.1, U805.23, U1101.18
M1_B: C1104.1, Q1102.1, Q1107.3, R1158.1, U805.22, U1101.15
M1_C: C1108.1, Q1113.1, Q1117.3, R1161.1, U805.21, U1101.12
M2_A: C1227.1, Q1211.1, Q1220.3, R1255.1, U805.20, U1201.18
M2_B: C1204.1, Q1202.1, Q1207.3, R1258.1, U805.19, U1201.15
M2_C: C1208.1, Q1213.1, Q1217.3, R1261.1, U805.18, U1201.12
M3_A: C1327.1, Q1311.1, Q1320.3, R1355.1, U805.15, U1301.18
M3_B: C1304.1, Q1302.1, Q1307.3, R1358.1, U805.16, U1301.15
M3_C: C1308.1, Q1313.1, Q1317.3, R1361.1, U805.17, U1301.12
M4_A: C1427.1, Q1411.1, Q1420.3, R1455.1, U805.12, U1401.18
M4_B: C1404.1, Q1402.1, Q1407.3, R1458.1, U805.13, U1401.15
M4_C: C1408.1, Q1413.1, Q1417.3, R1461.1, U805.14, U1401.12
MOTOR1: J625.1, J801.5, P601.5, R1175.1, U101.37, U805.7
MOTOR2: J627.1, J801.6, P601.6, R1275.1, U101.36, U805.8
MOTOR3: J629.1, J801.7, P601.7, R1375.1, U101.35, U805.9
MOTOR4: J632.1, J801.8, P601.8, R1475.1, U101.34, U805.10
unnamed: C102.2, R110.2, X101.3
unnamed: C701.1, L701.1, X701.1
unnamed: C724.1, L705.1, U701.2, U701.3
unnamed: D101.2, R113.2
unnamed: D202.2, R205.2
unnamed: D203.2, R208.2
unnamed: D205.2, R207.2
unnamed: FL701.1, U706.22
unnamed: FL701.3, JP701.1
unnamed: C718.1, OSC701.3
unnamed: Q1102.2, R1150.2
unnamed: Q1107.2, R1163.2
unnamed: Q1111.2, R1167.2
unnamed: Q1113.2, R1127.2
unnamed: Q1117.2, R1134.2
unnamed: Q1120.2, R1171.2
unnamed: Q1202.2, R1250.2
unnamed: Q1207.2, R1263.2
unnamed: Q1211.2, R1267.2
unnamed: Q1213.2, R1227.2
unnamed: Q1217.2, R1234.2
unnamed: Q1220.2, R1271.2
unnamed: Q1302.2, R1350.2
unnamed: Q1307.2, R1363.2
unnamed: Q1311.2, R1367.2
unnamed: Q1313.2, R1327.2
unnamed: Q1317.2, R1334.2
unnamed: Q1320.2, R1371.2
unnamed: Q1402.2, R1450.2
unnamed: Q1407.2, R1463.2
unnamed: Q1411.2, R1467.2
unnamed: Q1413.2, R1427.2
unnamed: Q1417.2, R1434.2
unnamed: Q1420.2, R1471.2
unnamed: R108.1, U102.2
unnamed: R112.2, R113.1
unnamed: R108.2, U101.60
unnamed: R105.2, U101.51
unnamed: R107.1, U101.52
unnamed: C110.1, R102.2, U101.46
unnamed: L101.2, U101.48
unnamed: C203.2, U202.6
unnamed: R201.1, R202.1, U202.4
unnamed: C203.1, L201.1, U202.2
unnamed: C204.2, U203.6
unnamed: R203.1, R204.1, U203.4
unnamed: C204.1, L202.1, U203.2
unnamed: U401.3, U402.4
unnamed: R406.1, R407.1, U401.4
unnamed: R407.2, R408.1, U401.1
unnamed: C721.1, L704.2, U701.1
unnamed: C719.2, C725.2, L706.1, U706.2, U706.12
unnamed: L706.2, U706.14
unnamed: C726.1, U706.1
unnamed: C718.2, U706.4
unnamed: C805.1, C806.2, R805.1, U801.4
unnamed: C804.1, C806.1, R804.1, U801.5
unnamed: R803.2, U801.6
unnamed: C811.2, U802.1
unnamed: R801.2, R802.1, U802.3
unnamed: C811.1, U802.6, U803.1
unnamed: C1127.2, U1101.20
unnamed: C1104.2, U1101.17
unnamed: C1108.2, U1101.14
unnamed: R1148.1, U1108.1
unnamed: C1124.1, R1147.1, U1108.4
unnamed: TP1107.1, U1108.21
unnamed: TP1108.1, U1108.22
unnamed: R1175.2, U1108.25
unnamed: C1227.2, U1201.20
unnamed: C1204.2, U1201.17
unnamed: C1208.2, U1201.14
unnamed: R1248.1, U1208.1
unnamed: C1224.1, R1247.1, U1208.4
unnamed: TP1207.1, U1208.21
unnamed: TP1208.1, U1208.22
unnamed: R1275.2, U1208.25
unnamed: C1327.2, U1301.20
unnamed: C1304.2, U1301.17
unnamed: C1308.2, U1301.14
unnamed: R1348.1, U1308.1
unnamed: C1324.1, R1347.1, U1308.4
unnamed: TP1307.1, U1308.21
unnamed: TP1308.1, U1308.22
unnamed: R1375.2, U1308.25
unnamed: C1427.2, U1401.20
unnamed: C1404.2, U1401.17
unnamed: C1408.2, U1401.14
unnamed: R1448.1, U1408.1
unnamed: C1424.1, R1447.1, U1408.4
unnamed: TP1407.1, U1408.21
unnamed: TP1408.1, U1408.22
unnamed: R1475.2, U1408.25
unnamed: R106.2, USB101.A5
unnamed: R109.2, USB101.B5
OSD_EN: U101.19, U402.6
OSD_SYNC: U101.27, U403.1
OSD_W: R402.1, U101.18
PADS_CURRENT_NC: J623.1, P601.3
PIOUART0_RX: J635.1, P601.4, U101.5
PIOUART0_TX: J634.1, U101.4
SPI0.MISO: Card502.7, U101.32
SPI0.MOSI: Card502.3, U101.31
SPI0.SCK: Card502.5, U101.29
SPI1.MISO: U101.16, U301.1
SPI1.MOSI: U101.15, U301.14
SPI1.SCK: U101.14, U301.13
UART0_RX: J640.1, U101.3, U601.4
UART0_TX: J639.1, U101.2, U601.3
UART1_RX: J649.1, U101.10, U601.6, U701.28
UART1_TX: J602.1, U101.9, U701.27
VIDEO_IN: J622.1, R401.1, R405.2, U402.3
VIDEO_OUT: J624.1, R408.2
